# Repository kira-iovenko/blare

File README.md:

# Kira BLARE Clock

A 6-key alarm clock with a wide 2.25" screen and a buzzer that won't let you go back to sleep. To turn the alarm off you have to type a random code. I built the PCB, case and firmware from scratch.

## Features

- Big 7-segment style clock with seconds, the date, and the alarm status
- Gets the time from the internet over WiFi (NTP), with automatic daylight saving
- The alarm can repeat every day, on weekdays, on weekends, or ring once, and it has a snooze
- **Stop code:** to stop the alarm you type a random key sequence shown on the screen
- Night mode dims the digits to red so the clock doesn't light up the room
- Runs on a Seeed XIAO ESP32C3 with Arduino firmware

## Hardware

- Controller: Seeed XIAO ESP32C3
- Display: 2.25" ST7789 TFT (76x284), SPI
- Switches: 6x MX-style, each wired straight to a GPIO
- Buzzer: 3.3V piezo
- Connector: 8-pin header for the screen, which is wired off the PCB with jumper wires

## PCB

Designed in KiCad. It's a simple 2-layer board (67 x 68 mm) with the switches on the front and the XIAO, buzzer and screen header on the back, inside the case. There's no matrix, so the board needs no diodes. The source files are in [`pcb/`](pcb/): schematic, layout and STEP export.

## Case

Designed in Fusion 360. It's made of four printed parts (front, back, base and case) held together with M3 screws and heat-set inserts. The full assembly is in [`cad/blare.step`](cad/), and each printable part is in [`production/`](production/).

## Firmware

The firmware is an Arduino sketch in [`firmware/`](firmware/). Setup, pins and troubleshooting are in [`firmware/README.md`](firmware/README.md).

### Keymap

| | | |
|-|-|-|
| [1] Menu | [2] Up   | [3] Alarm on/off  |
| [4] Back | [5] Down | [6] OK / Snooze   |

When the alarm rings, **OK** snoozes it. Any other key brings up the stop code: the screen shows a random sequence like `5 2 6 1`, and you type it on the keys, which are numbered 1-6 from left to right, top to bottom. A wrong key gives you a new code.

### Flash

1. Install the [Arduino IDE](https://www.arduino.cc/en/software/) and the ESP32 boards ([Seeed guide](https://wiki.seeedstudio.com/XIAO_ESP32C3_Getting_Started/)).
2. Install the **Adafruit ST7735 and ST7789** and **Adafruit GFX** libraries from the Library Manager.
3. Copy `firmware/secrets.example.h` to `secrets.h` and add your WiFi name and password.
4. Open `firmware/blare.ino`, select **XIAO_ESP32C3**, and click Upload.

### Customizing

- Key functions: change the `KEY_*` lines in `firmware/config.h`.
- Time zone, colours, night hours, buzzer tone: `firmware/config.h`.
- Alarm sound: edit `ALARM_PATTERN` in `firmware/blare.ino`.

## Built with

- KiCad (PCB)
- Fusion 360 (case)
- Arduino + Adafruit GFX (firmware)

## BOM (Bill of Materials)

The full parts list is in **[`BOM.csv`](BOM.csv)**.

| Component | Qty | Purchase/source |
|---|---:|---|
| Seeed Studio XIAO ESP32C3 | 1 | [Link](https://www.seeedstudio.com/Seeed-XIAO-ESP32C3-p-5431.html) |
| 2.25" ST7789 TFT display (76x284) | 1 | [Link](https://www.aliexpress.us/item/3256809062781172.html) |
| MX-style mechanical switches | 6 | [Link](https://www.aliexpress.com/w/wholesale-mx-mechanical-switch.html) |
| White blank DSA keycaps | 6 | [Link](https://www.aliexpress.com/w/wholesale-blank-dsa-keycaps.html) |
| 3.3V piezo buzzer | 1 | [Link](https://www.aliexpress.us/item/3256813197582507.html) |
| 2.54 mm 8-pin male header | 1 | [Link](https://www.aliexpress.us/item/3256809277554207.html) |
| 20 cm female-female jumper wires | 8 | [Link](https://www.aliexpress.us/item/3256802412794075.html) |
| M3x5x4 heat-set inserts | 14 | [Link](https://www.aliexpress.com/w/wholesale-m3-heat-set-insert.html) |
| M3x6 mm screws | 14 | [Link](https://www.mcmaster.com/products/socket-head-screws/thread-size~m3/) |
| Custom BLARE PCB (2-layer) | 1 | [Link](https://jlcpcb.com/), [`production/gerbers.zip`](production/) |
| 3D-printed case (4 parts) | 1 | [`production/`](production/) |

## Inspiration

I built this by following Hack Club's [BLARE](https://blare.hackclub.com/docs) guide.

## Author

Made with ❤️ by [@kira-iovenko](https://github.com/kira-iovenko)

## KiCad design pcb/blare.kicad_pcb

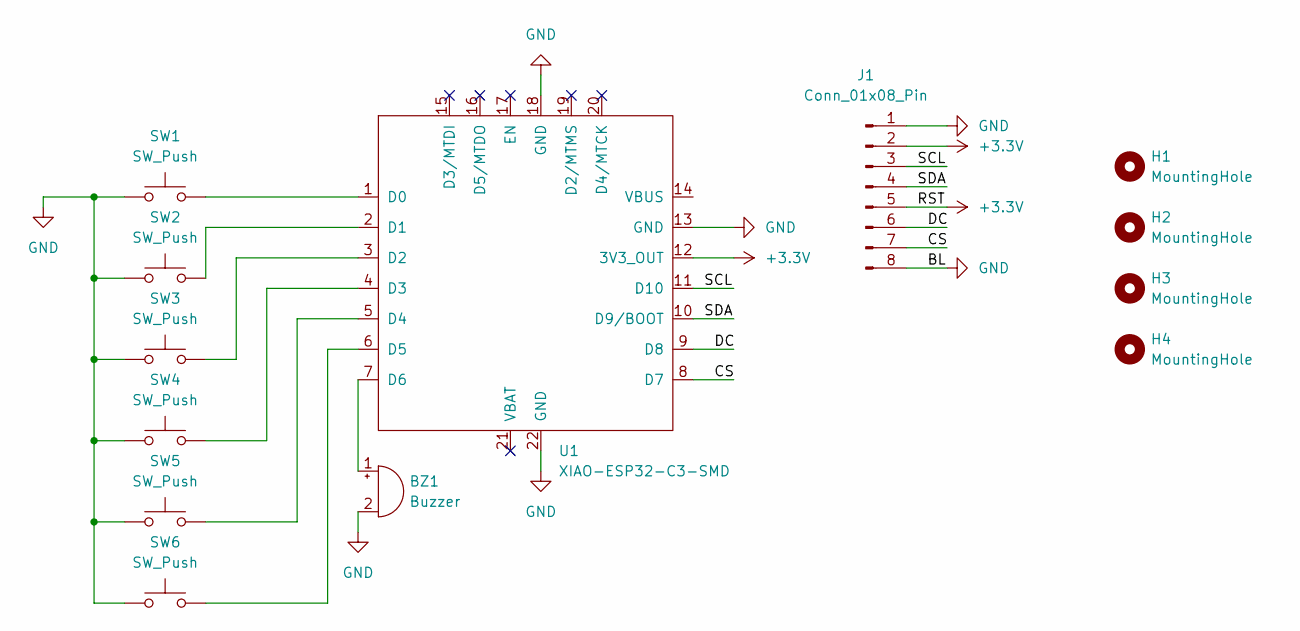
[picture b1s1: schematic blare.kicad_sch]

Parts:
BZ1: Buzzer; Buzzer_12x9.5RM7.6
H1, H2, H3, H4: MountingHole; MountingHole_3.2mm_M3
J1: Conn_01x08_Pin; PinSocket_1x08_P2.54mm_Vertical
SW1, SW2, SW3, SW4, SW5, SW6: SW_Push; SW_Cherry_MX_1.00u_PCB
U1: XIAO-ESP32-C3-SMD; XIAO-ESP32-C3-DIP-SMD

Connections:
+3.3V: J1.2, J1.5, U1.12 (3V3_OUT)
/CS: J1.7, U1.8 (D7)
/DC: J1.6, U1.9 (D8)
/SCL: J1.3, U1.11 (D10)
/SDA: J1.4, U1.10 (D9/BOOT)
GND: BZ1.2 (-), J1.1, J1.8, SW1.1, SW2.1, SW3.1, SW4.1, SW5.1, SW6.1, U1.13 (GND), U1.18 (GND), U1.22 (GND)
unnamed: BZ1.1 (+), U1.7 (D6)
unnamed: SW1.2, U1.1 (D0)
unnamed: SW2.2, U1.2 (D1)
unnamed: SW3.2, U1.3 (D2)
unnamed: SW4.2, U1.4 (D3)
unnamed: SW5.2, U1.5 (D4)
unnamed: SW6.2, U1.6 (D5)

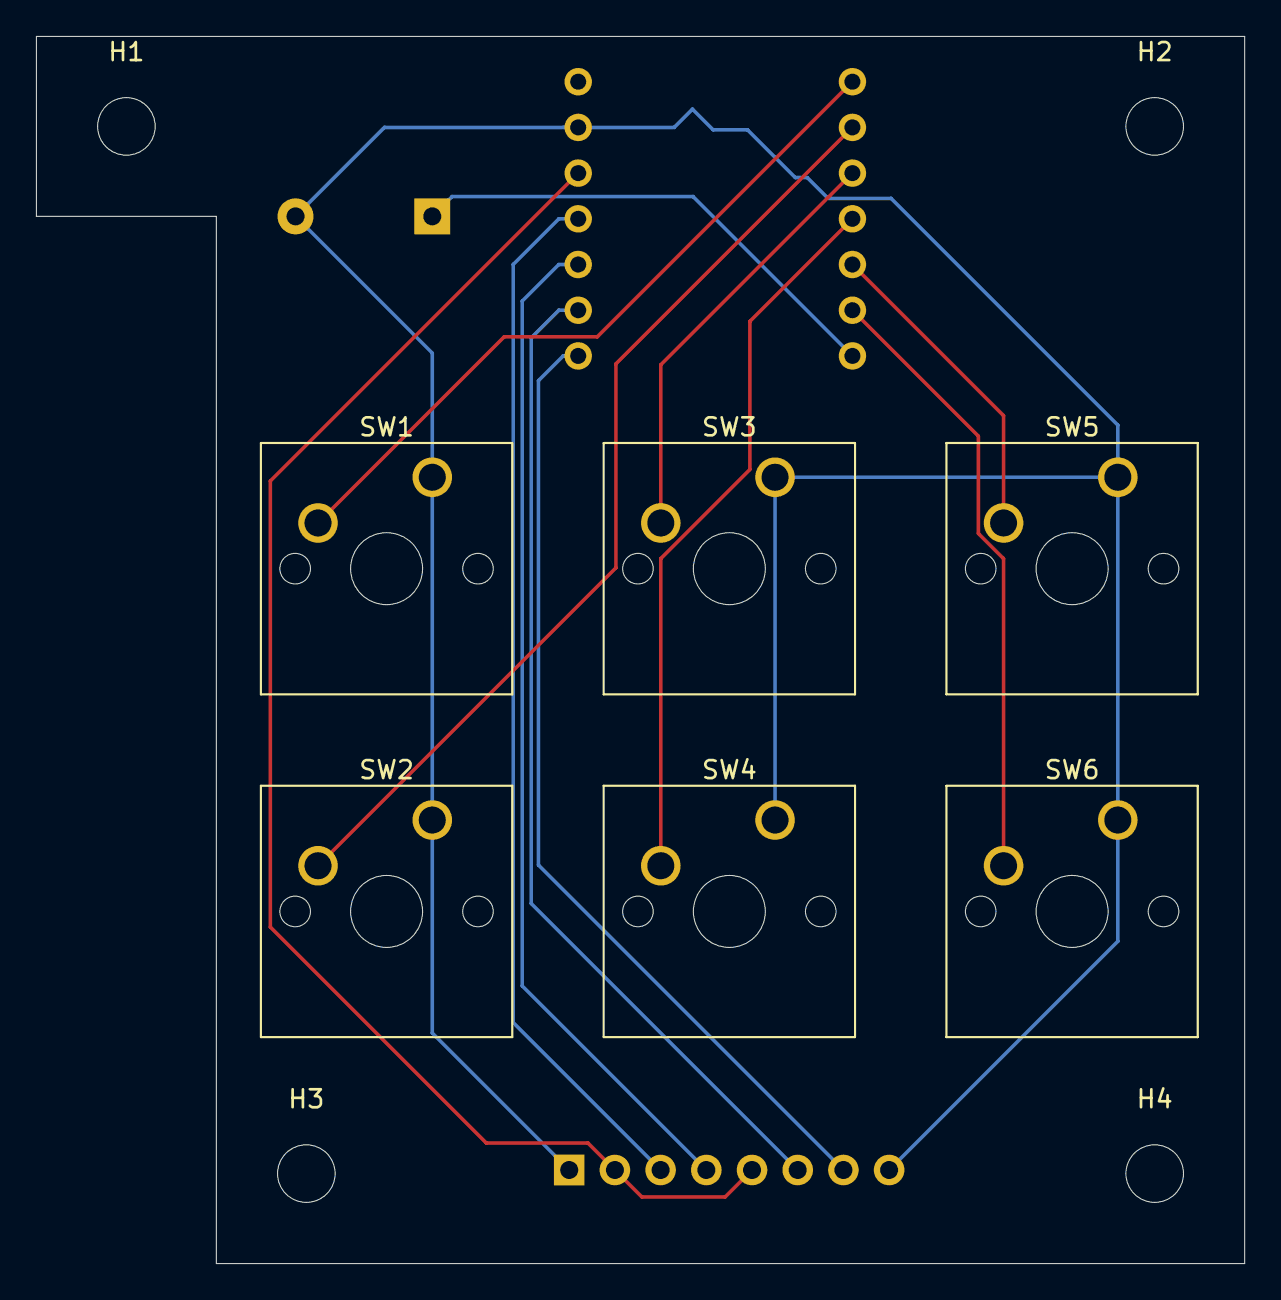
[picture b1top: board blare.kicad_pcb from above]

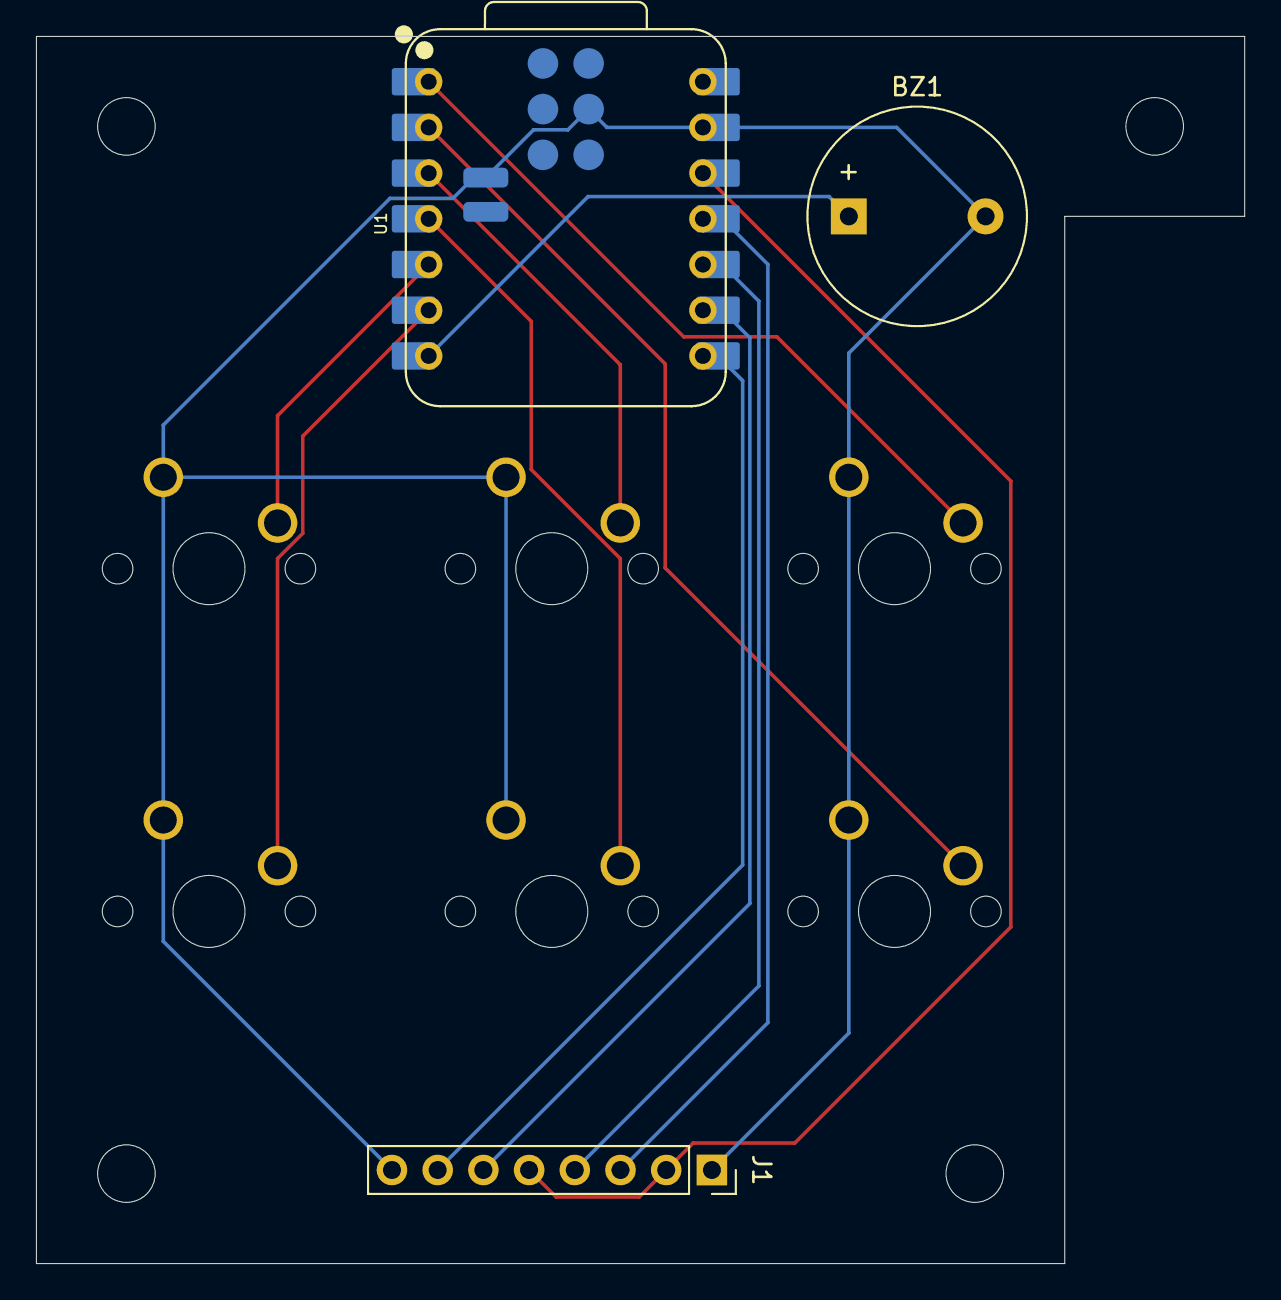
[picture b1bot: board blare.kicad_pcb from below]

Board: 2 copper layers, 67.2 x 68.2 mm, 13 parts (3 on the bottom side), 13 nets.
